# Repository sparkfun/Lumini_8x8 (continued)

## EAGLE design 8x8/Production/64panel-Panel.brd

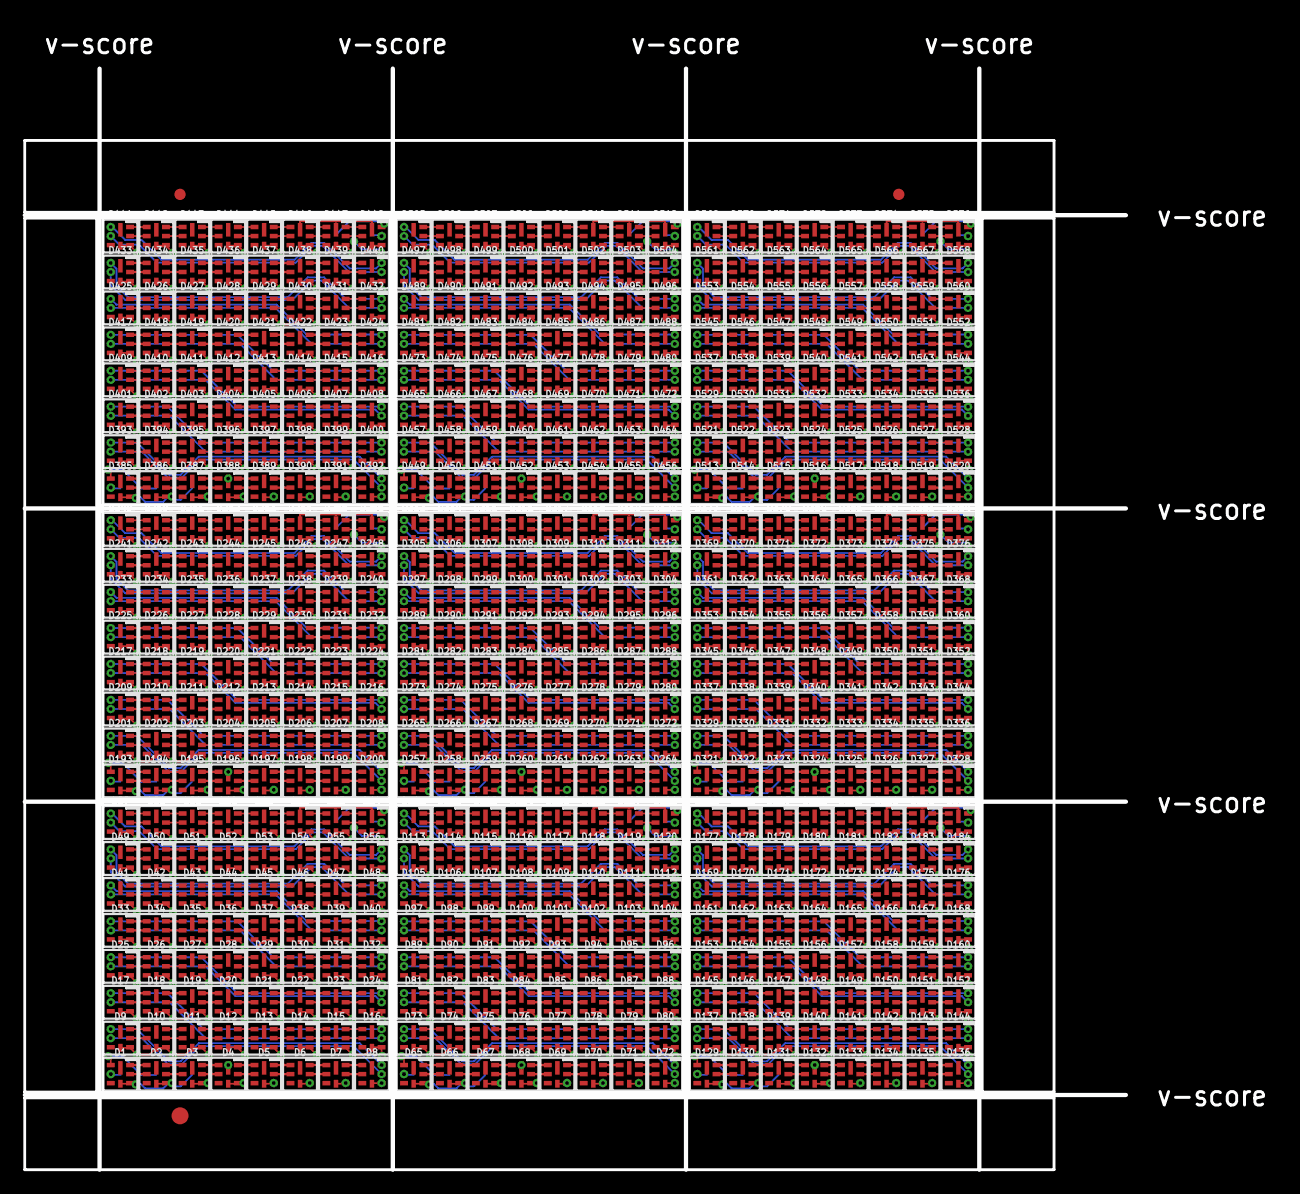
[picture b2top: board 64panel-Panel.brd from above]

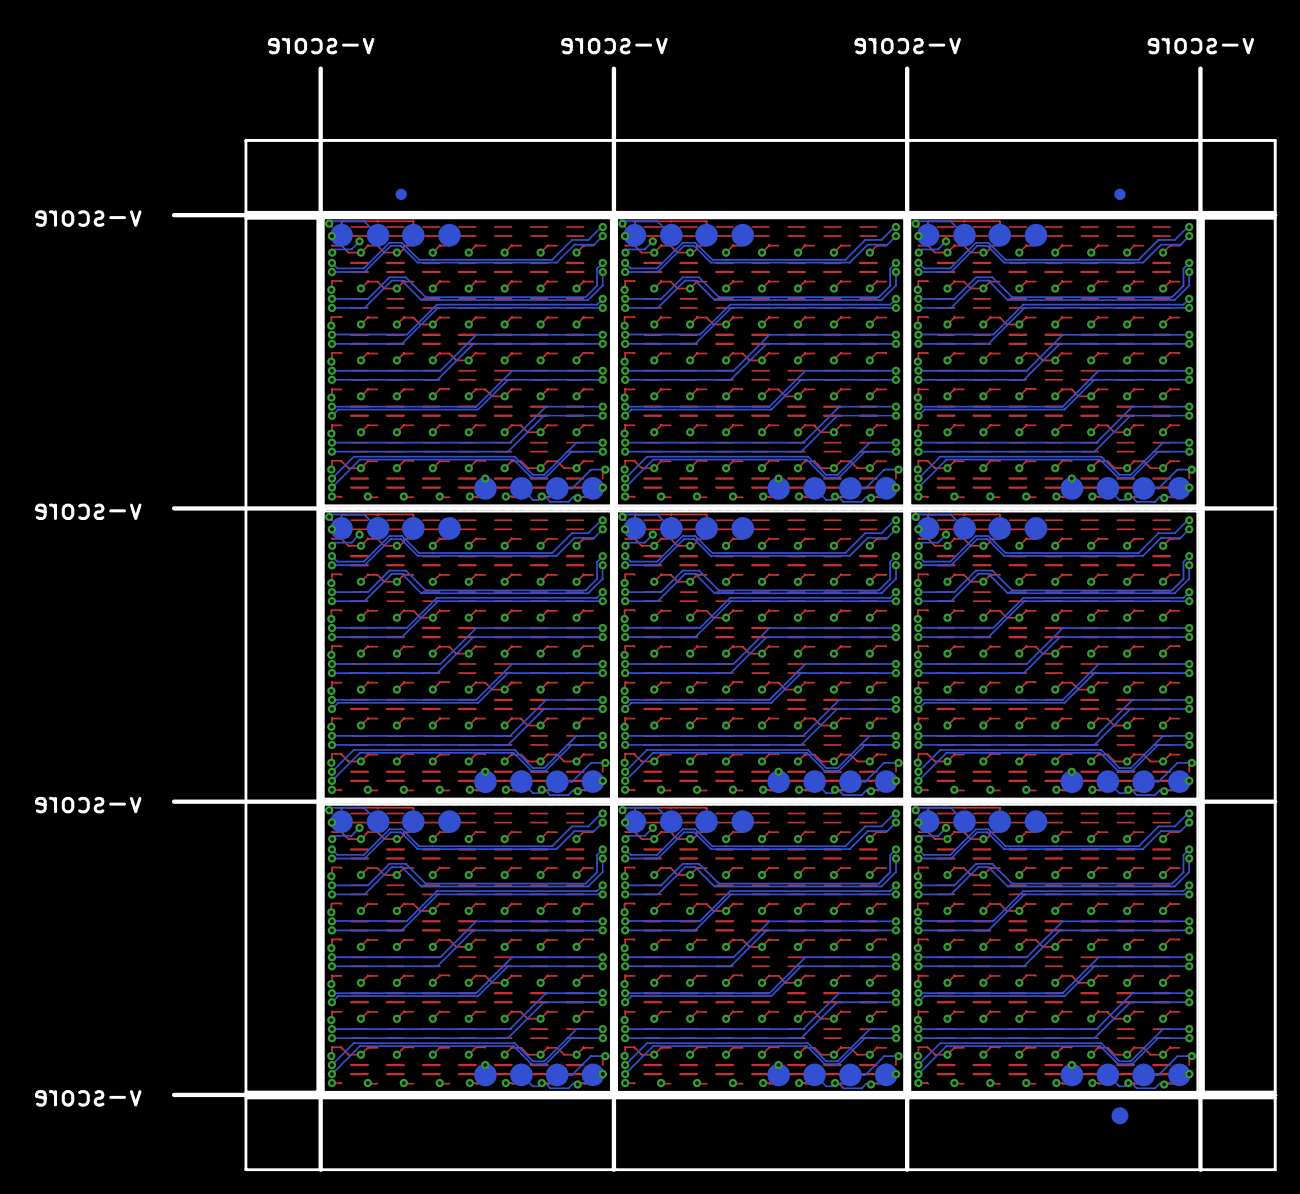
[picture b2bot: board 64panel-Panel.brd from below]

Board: 2 copper layers, 97.3 x 97.3 mm, 654 parts (75 on the bottom side), 1188 nets.

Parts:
D1, D2, D3, D4, D5, D6, D7, D8, D9, D10, D11, D12, D13, D14, D15, D16, D17, D18, D19, D20, D21, D22, D23, D24, D25, D26, D27, D28, D29, D30, D31, D32, D33, D34, D35, D36, D37, D38, D39, D40, D41, D42, D43, D44, D45, D46, D47, D48, D49, D50, D51, D52, D53, D54, D55, D56, D57, D58, D59, D60, D61, D62, D63, D64, D65, D66, D67, D68, D69, D70, D71, D72, D73, D74, D75, D76, D77, D78, D79, D80, D81, D82, D83, D84, D85, D86, D87, D88, D89, D90, D91, D92, D93, D94, D95, D96, D97, D98, D99, D100, D101, D102, D103, D104, D105, D106, D107, D108, D109, D110, D111, D112, D113, D114, D115, D116, D117, D118, D119, D120, D121, D122, D123, D124, D125, D126, D127, D128, D129, D130, D131, D132, D133, D134, D135, D136, D137, D138, D139, D140, D141, D142, D143, D144, D145, D146, D147, D148, D149, D150, D151, D152, D153, D154, D155, D156, D157, D158, D159, D160, D161, D162, D163, D164, D165, D166, D167, D168, D169, D170, D171, D172, D173, D174, D175, D176, D177, D178, D179, D180, D181, D182, D183, D184, D185, D186, D187, D188, D189, D190, D191, D192, D193, D194, D195, D196, D197, D198, D199, D200, D201, D202, D203, D204, D205, D206, D207, D208, D209, D210, D211, D212, D213, D214, D215, D216, D217, D218, D219, D220, D221, D222, D223, D224, D225, D226, D227, D228, D229, D230, D231, D232, D233, D234, D235, D236, D237, D238, D239, D240, D241, D242, D243, D244, D245, D246, D247, D248, D249, D250, D251, D252, D253, D254, D255, D256, D257, D258, D259, D260, D261, D262, D263, D264, D265, D266, D267, D268, D269, D270, D271, D272, D273, D274, D275, D276, D277, D278, D279, D280, D281, D282, D283, D284, D285, D286, D287, D288, D289, D290, D291, D292, D293, D294, D295, D296, D297, D298, D299, D300, D301, D302, D303, D304, D305, D306, D307, D308, D309, D310, D311, D312, D313, D314, D315, D316, D317, D318, D319, D320, D321, D322, D323, D324, D325, D326, D327, D328, D329, D330, D331, D332, D333, D334, D335, D336, D337, D338, D339, D340, D341, D342, D343, D344, D345, D346, D347, D348, D349, D350, D351, D352, D353, D354, D355, D356, D357, D358, D359, D360, D361, D362, D363, D364, D365, D366, D367, D368, D369, D370, D371, D372, D373, D374, D375, D376, D377, D378, D379, D380, D381, D382, D383, D384, D385, D386, D387, D388, D389, D390, D391, D392, D393, D394, D395, D396, D397, D398, D399, D400, D401, D402, D403, D404, D405, D406, D407, D408, D409, D410, D411, D412, D413, D414, D415, D416, D417, D418, D419, D420, D421, D422, D423, D424, D425, D426, D427, D428, D429, D430, D431, D432, D433, D434, D435, D436, D437, D438, D439, D440, D441, D442, D443, D444, D445, D446, D447, D448, D449, D450, D451, D452, D453, D454, D455, D456, D457, D458, D459, D460, D461, D462, D463, D464, D465, D466, D467, D468, D469, D470, D471, D472, D473, D474, D475, D476, D477, D478, D479, D480, D481, D482, D483, D484, D485, D486, D487, D488, D489, D490, D491, D492, D493, D494, D495, D496, D497, D498, D499, D500, D501, D502, D503, D504, D505, D506, D507, D508, D509, D510, D511, D512, D513, D514, D515, D516, D517, D518, D519, D520, D521, D522, D523, D524, D525, D526, D527, D528, D529, D530, D531, D532, D533, D534, D535, D536, D537, D538, D539, D540, D541, D542, D543, D544, D545, D546, D547, D548, D549, D550, D551, D552, D553, D554, D555, D556, D557, D558, D559, D560, D561, D562, D563, D564, D565, D566, D567, D568, D569, D570, D571, D572, D573, D574, D575, D576: APA1022020; APA102-2020
E$1, E$2, E$3, E$4: FIDUCIAL-1X2
E$5, E$6: FIDUCIAL-1.5X3
J1, J2, J3, J4, J5, J6, J7, J8, J9, J10, J11, J12, J13, J14, J15, J16, J17, J18, J19, J20, J21, J22, J23, J24, J25, J26, J27, J28, J29, J30, J31, J32, J33, J34, J35, J36, J37, J38, J39, J40, J41, J42, J43, J44, J45, J46, J47, J48, J49, J50, J51, J52, J53, J54, J55, J56, J57, J58, J59, J60, J61, J62, J63, J64, J65, J66, J67, J68, J69, J70, J71, J72: LED_PADCIRCULARPAD; CIRCULARPAD

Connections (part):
5V: D1.VDD, D1.VDDPAD, D2.VDD, D2.VDDPAD, D3.VDD, D3.VDDPAD, D4.VDD, D4.VDDPAD, D5.VDD, D5.VDDPAD, D6.VDD, D6.VDDPAD, D7.VDD, D7.VDDPAD, D8.VDD, D8.VDDPAD, D9.VDD, D9.VDDPAD, D10.VDD, D10.VDDPAD, D11.VDD, D11.VDDPAD, D12.VDD, D12.VDDPAD, D13.VDD, D13.VDDPAD, D14.VDD, D14.VDDPAD, D15.VDD, D15.VDDPAD, D16.VDD, D16.VDDPAD, D17.VDD, D17.VDDPAD, D18.VDD, D18.VDDPAD, D19.VDD, D19.VDDPAD, D20.VDD, D20.VDDPAD, D21.VDD, D21.VDDPAD, D22.VDD, D22.VDDPAD, D23.VDD, D23.VDDPAD, D24.VDD, D24.VDDPAD, D25.VDD, D25.VDDPAD, D26.VDD, D26.VDDPAD, D27.VDD, D27.VDDPAD, D28.VDD, D28.VDDPAD, D29.VDD, D29.VDDPAD, D30.VDD, D30.VDDPAD, D31.VDD, D31.VDDPAD, D32.VDD, D32.VDDPAD, D33.VDD, D33.VDDPAD, D34.VDD, D34.VDDPAD, D35.VDD, D35.VDDPAD, D36.VDD, D36.VDDPAD, D37.VDD, D37.VDDPAD, D38.VDD, D38.VDDPAD, D39.VDD, D39.VDDPAD, D40.VDD, D40.VDDPAD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
5V1: D65.VDD, D65.VDDPAD, D66.VDD, D66.VDDPAD, D67.VDD, D67.VDDPAD, D68.VDD, D68.VDDPAD, D69.VDD, D69.VDDPAD, D70.VDD, D70.VDDPAD, D71.VDD, D71.VDDPAD, D72.VDD, D72.VDDPAD, D73.VDD, D73.VDDPAD, D74.VDD, D74.VDDPAD, D75.VDD, D75.VDDPAD, D76.VDD, D76.VDDPAD, D77.VDD, D77.VDDPAD, D78.VDD, D78.VDDPAD, D79.VDD, D79.VDDPAD, D80.VDD, D80.VDDPAD, D81.VDD, D81.VDDPAD, D82.VDD, D82.VDDPAD, D83.VDD, D83.VDDPAD, D84.VDD, D84.VDDPAD, D85.VDD, D85.VDDPAD, D86.VDD, D86.VDDPAD, D87.VDD, D87.VDDPAD, D88.VDD, D88.VDDPAD, D89.VDD, D89.VDDPAD, D90.VDD, D90.VDDPAD, D91.VDD, D91.VDDPAD, D92.VDD, D92.VDDPAD, D93.VDD, D93.VDDPAD, D94.VDD, D94.VDDPAD, D95.VDD, D95.VDDPAD, D96.VDD, D96.VDDPAD, D97.VDD, D97.VDDPAD, D98.VDD, D98.VDDPAD, D99.VDD, D99.VDDPAD, D100.VDD, D100.VDDPAD, D101.VDD, D101.VDDPAD, D102.VDD, D102.VDDPAD, D103.VDD, D103.VDDPAD, D104.VDD, D104.VDDPAD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
5V2: D129.VDD, D129.VDDPAD, D130.VDD, D130.VDDPAD, D131.VDD, D131.VDDPAD, D132.VDD, D132.VDDPAD, D133.VDD, D133.VDDPAD, D134.VDD, D134.VDDPAD, D135.VDD, D135.VDDPAD, D136.VDD, D136.VDDPAD, D137.VDD, D137.VDDPAD, D138.VDD, D138.VDDPAD, D139.VDD, D139.VDDPAD, D140.VDD, D140.VDDPAD, D141.VDD, D141.VDDPAD, D142.VDD, D142.VDDPAD, D143.VDD, D143.VDDPAD, D144.VDD, D144.VDDPAD, D145.VDD, D145.VDDPAD, D146.VDD, D146.VDDPAD, D147.VDD, D147.VDDPAD, D148.VDD, D148.VDDPAD, D149.VDD, D149.VDDPAD, D150.VDD, D150.VDDPAD, D151.VDD, D151.VDDPAD, D152.VDD, D152.VDDPAD, D153.VDD, D153.VDDPAD, D154.VDD, D154.VDDPAD, D155.VDD, D155.VDDPAD, D156.VDD, D156.VDDPAD, D157.VDD, D157.VDDPAD, D158.VDD, D158.VDDPAD, D159.VDD, D159.VDDPAD, D160.VDD, D160.VDDPAD, D161.VDD, D161.VDDPAD, D162.VDD, D162.VDDPAD, D163.VDD, D163.VDDPAD, D164.VDD, D164.VDDPAD, D165.VDD, D165.VDDPAD, D166.VDD, D166.VDDPAD, D167.VDD, D167.VDDPAD, D168.VDD, D168.VDDPAD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
5V3: D193.VDD, D193.VDDPAD, D194.VDD, D194.VDDPAD, D195.VDD, D195.VDDPAD, D196.VDD, D196.VDDPAD, D197.VDD, D197.VDDPAD, D198.VDD, D198.VDDPAD, D199.VDD, D199.VDDPAD, D200.VDD, D200.VDDPAD, D201.VDD, D201.VDDPAD, D202.VDD, D202.VDDPAD, D203.VDD, D203.VDDPAD, D204.VDD, D204.VDDPAD, D205.VDD, D205.VDDPAD, D206.VDD, D206.VDDPAD, D207.VDD, D207.VDDPAD, D208.VDD, D208.VDDPAD, D209.VDD, D209.VDDPAD, D210.VDD, D210.VDDPAD, D211.VDD, D211.VDDPAD, D212.VDD, D212.VDDPAD, D213.VDD, D213.VDDPAD, D214.VDD, D214.VDDPAD, D215.VDD, D215.VDDPAD, D216.VDD, D216.VDDPAD, D217.VDD, D217.VDDPAD, D218.VDD, D218.VDDPAD, D219.VDD, D219.VDDPAD, D220.VDD, D220.VDDPAD, D221.VDD, D221.VDDPAD, D222.VDD, D222.VDDPAD, D223.VDD, D223.VDDPAD, D224.VDD, D224.VDDPAD, D225.VDD, D225.VDDPAD, D226.VDD, D226.VDDPAD, D227.VDD, D227.VDDPAD, D228.VDD, D228.VDDPAD, D229.VDD, D229.VDDPAD, D230.VDD, D230.VDDPAD, D231.VDD, D231.VDDPAD, D232.VDD, D232.VDDPAD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
5V4: D257.VDD, D257.VDDPAD, D258.VDD, D258.VDDPAD, D259.VDD, D259.VDDPAD, D260.VDD, D260.VDDPAD, D261.VDD, D261.VDDPAD, D262.VDD, D262.VDDPAD, D263.VDD, D263.VDDPAD, D264.VDD, D264.VDDPAD, D265.VDD, D265.VDDPAD, D266.VDD, D266.VDDPAD, D267.VDD, D267.VDDPAD, D268.VDD, D268.VDDPAD, D269.VDD, D269.VDDPAD, D270.VDD, D270.VDDPAD, D271.VDD, D271.VDDPAD, D272.VDD, D272.VDDPAD, D273.VDD, D273.VDDPAD, D274.VDD, D274.VDDPAD, D275.VDD, D275.VDDPAD, D276.VDD, D276.VDDPAD, D277.VDD, D277.VDDPAD, D278.VDD, D278.VDDPAD, D279.VDD, D279.VDDPAD, D280.VDD, D280.VDDPAD, D281.VDD, D281.VDDPAD, D282.VDD, D282.VDDPAD, D283.VDD, D283.VDDPAD, D284.VDD, D284.VDDPAD, D285.VDD, D285.VDDPAD, D286.VDD, D286.VDDPAD, D287.VDD, D287.VDDPAD, D288.VDD, D288.VDDPAD, D289.VDD, D289.VDDPAD, D290.VDD, D290.VDDPAD, D291.VDD, D291.VDDPAD, D292.VDD, D292.VDDPAD, D293.VDD, D293.VDDPAD, D294.VDD, D294.VDDPAD, D295.VDD, D295.VDDPAD, D296.VDD, D296.VDDPAD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
5V5: D321.VDD, D321.VDDPAD, D322.VDD, D322.VDDPAD, D323.VDD, D323.VDDPAD, D324.VDD, D324.VDDPAD, D325.VDD, D325.VDDPAD, D326.VDD, D326.VDDPAD, D327.VDD, D327.VDDPAD, D328.VDD, D328.VDDPAD, D329.VDD, D329.VDDPAD, D330.VDD, D330.VDDPAD, D331.VDD, D331.VDDPAD, D332.VDD, D332.VDDPAD, D333.VDD, D333.VDDPAD, D334.VDD, D334.VDDPAD, D335.VDD, D335.VDDPAD, D336.VDD, D336.VDDPAD, D337.VDD, D337.VDDPAD, D338.VDD, D338.VDDPAD, D339.VDD, D339.VDDPAD, D340.VDD, D340.VDDPAD, D341.VDD, D341.VDDPAD, D342.VDD, D342.VDDPAD, D343.VDD, D343.VDDPAD, D344.VDD, D344.VDDPAD, D345.VDD, D345.VDDPAD, D346.VDD, D346.VDDPAD, D347.VDD, D347.VDDPAD, D348.VDD, D348.VDDPAD, D349.VDD, D349.VDDPAD, D350.VDD, D350.VDDPAD, D351.VDD, D351.VDDPAD, D352.VDD, D352.VDDPAD, D353.VDD, D353.VDDPAD, D354.VDD, D354.VDDPAD, D355.VDD, D355.VDDPAD, D356.VDD, D356.VDDPAD, D357.VDD, D357.VDDPAD, D358.VDD, D358.VDDPAD, D359.VDD, D359.VDDPAD, D360.VDD, D360.VDDPAD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
5V6: D385.VDD, D385.VDDPAD, D386.VDD, D386.VDDPAD, D387.VDD, D387.VDDPAD, D388.VDD, D388.VDDPAD, D389.VDD, D389.VDDPAD, D390.VDD, D390.VDDPAD, D391.VDD, D391.VDDPAD, D392.VDD, D392.VDDPAD, D393.VDD, D393.VDDPAD, D394.VDD, D394.VDDPAD, D395.VDD, D395.VDDPAD, D396.VDD, D396.VDDPAD, D397.VDD, D397.VDDPAD, D398.VDD, D398.VDDPAD, D399.VDD, D399.VDDPAD, D400.VDD, D400.VDDPAD, D401.VDD, D401.VDDPAD, D402.VDD, D402.VDDPAD, D403.VDD, D403.VDDPAD, D404.VDD, D404.VDDPAD, D405.VDD, D405.VDDPAD, D406.VDD, D406.VDDPAD, D407.VDD, D407.VDDPAD, D408.VDD, D408.VDDPAD, D409.VDD, D409.VDDPAD, D410.VDD, D410.VDDPAD, D411.VDD, D411.VDDPAD, D412.VDD, D412.VDDPAD, D413.VDD, D413.VDDPAD, D414.VDD, D414.VDDPAD, D415.VDD, D415.VDDPAD, D416.VDD, D416.VDDPAD, D417.VDD, D417.VDDPAD, D418.VDD, D418.VDDPAD, D419.VDD, D419.VDDPAD, D420.VDD, D420.VDDPAD, D421.VDD, D421.VDDPAD, D422.VDD, D422.VDDPAD, D423.VDD, D423.VDDPAD, D424.VDD, D424.VDDPAD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
5V7: D449.VDD, D449.VDDPAD, D450.VDD, D450.VDDPAD, D451.VDD, D451.VDDPAD, D452.VDD, D452.VDDPAD, D453.VDD, D453.VDDPAD, D454.VDD, D454.VDDPAD, D455.VDD, D455.VDDPAD, D456.VDD, D456.VDDPAD, D457.VDD, D457.VDDPAD, D458.VDD, D458.VDDPAD, D459.VDD, D459.VDDPAD, D460.VDD, D460.VDDPAD, D461.VDD, D461.VDDPAD, D462.VDD, D462.VDDPAD, D463.VDD, D463.VDDPAD, D464.VDD, D464.VDDPAD, D465.VDD, D465.VDDPAD, D466.VDD, D466.VDDPAD, D467.VDD, D467.VDDPAD, D468.VDD, D468.VDDPAD, D469.VDD, D469.VDDPAD, D470.VDD, D470.VDDPAD, D471.VDD, D471.VDDPAD, D472.VDD, D472.VDDPAD, D473.VDD, D473.VDDPAD, D474.VDD, D474.VDDPAD, D475.VDD, D475.VDDPAD, D476.VDD, D476.VDDPAD, D477.VDD, D477.VDDPAD, D478.VDD, D478.VDDPAD, D479.VDD, D479.VDDPAD, D480.VDD, D480.VDDPAD, D481.VDD, D481.VDDPAD, D482.VDD, D482.VDDPAD, D483.VDD, D483.VDDPAD, D484.VDD, D484.VDDPAD, D485.VDD, D485.VDDPAD, D486.VDD, D486.VDDPAD, D487.VDD, D487.VDDPAD, D488.VDD, D488.VDDPAD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
5V8: D513.VDD, D513.VDDPAD, D514.VDD, D514.VDDPAD, D515.VDD, D515.VDDPAD, D516.VDD, D516.VDDPAD, D517.VDD, D517.VDDPAD, D518.VDD, D518.VDDPAD, D519.VDD, D519.VDDPAD, D520.VDD, D520.VDDPAD, D521.VDD, D521.VDDPAD, D522.VDD, D522.VDDPAD, D523.VDD, D523.VDDPAD, D524.VDD, D524.VDDPAD, D525.VDD, D525.VDDPAD, D526.VDD, D526.VDDPAD, D527.VDD, D527.VDDPAD, D528.VDD, D528.VDDPAD, D529.VDD, D529.VDDPAD, D530.VDD, D530.VDDPAD, D531.VDD, D531.VDDPAD, D532.VDD, D532.VDDPAD, D533.VDD, D533.VDDPAD, D534.VDD, D534.VDDPAD, D535.VDD, D535.VDDPAD, D536.VDD, D536.VDDPAD, D537.VDD, D537.VDDPAD, D538.VDD, D538.VDDPAD, D539.VDD, D539.VDDPAD, D540.VDD, D540.VDDPAD, D541.VDD, D541.VDDPAD, D542.VDD, D542.VDDPAD, D543.VDD, D543.VDDPAD, D544.VDD, D544.VDDPAD, D545.VDD, D545.VDDPAD, D546.VDD, D546.VDDPAD, D547.VDD, D547.VDDPAD, D548.VDD, D548.VDDPAD, D549.VDD, D549.VDDPAD, D550.VDD, D550.VDDPAD, D551.VDD, D551.VDDPAD, D552.VDD, D552.VDDPAD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
CI: D1.CKI, J4.P$1
CI1: D65.CKI, J12.P$1
CI2: D129.CKI, J20.P$1
CI3: D193.CKI, J28.P$1
CI4: D257.CKI, J36.P$1
CI5: D321.CKI, J44.P$1
CI6: D385.CKI, J52.P$1
CI7: D449.CKI, J60.P$1
CI8: D513.CKI, J68.P$1
CO: D64.CKO, J1.P$1
CO1: D128.CKO, J9.P$1
CO2: D192.CKO, J17.P$1
CO3: D256.CKO, J25.P$1
CO4: D320.CKO, J33.P$1
CO5: D384.CKO, J41.P$1
CO6: D448.CKO, J49.P$1
CO7: D512.CKO, J57.P$1
CO8: D576.CKO, J65.P$1
CT1: D9.CKO, D10.CKI
CT2: D18.CKO, D19.CKI
CT3: D27.CKO, D28.CKI
CT4: D36.CKO, D37.CKI
CT5: D45.CKO, D46.CKI
CT6: D54.CKO, D55.CKI
CT7: D63.CKO, D64.CKI
CT8: D127.CKO, D128.CKI
CT9: D73.CKO, D74.CKI
CT10: D82.CKO, D83.CKI
CT11: D91.CKO, D92.CKI
CT12: D100.CKO, D101.CKI
CT13: D109.CKO, D110.CKI
CT14: D118.CKO, D119.CKI
CT15: D191.CKO, D192.CKI
CT16: D137.CKO, D138.CKI
CT17: D146.CKO, D147.CKI
CT18: D155.CKO, D156.CKI
CT19: D164.CKO, D165.CKI
CT20: D173.CKO, D174.CKI
CT21: D182.CKO, D183.CKI
CT22: D255.CKO, D256.CKI
CT23: D201.CKO, D202.CKI
CT24: D210.CKO, D211.CKI
CT25: D219.CKO, D220.CKI
CT26: D228.CKO, D229.CKI
CT27: D237.CKO, D238.CKI
CT28: D246.CKO, D247.CKI
CT29: D319.CKO, D320.CKI
CT30: D265.CKO, D266.CKI
CT31: D274.CKO, D275.CKI
CT32: D283.CKO, D284.CKI
CT33: D292.CKO, D293.CKI
CT34: D301.CKO, D302.CKI
CT35: D310.CKO, D311.CKI
CT36: D383.CKO, D384.CKI
CT37: D329.CKO, D330.CKI
CT38: D338.CKO, D339.CKI
CT39: D347.CKO, D348.CKI
CT40: D356.CKO, D357.CKI
CT41: D365.CKO, D366.CKI
CT42: D374.CKO, D375.CKI
CT43: D447.CKO, D448.CKI
CT44: D393.CKO, D394.CKI
CT45: D402.CKO, D403.CKI
CT46: D411.CKO, D412.CKI
CT47: D420.CKO, D421.CKI
CT48: D429.CKO, D430.CKI
CT49: D438.CKO, D439.CKI
CT50: D511.CKO, D512.CKI
CT51: D457.CKO, D458.CKI
CT52: D466.CKO, D467.CKI
CT53: D475.CKO, D476.CKI
CT54: D484.CKO, D485.CKI
CT55: D493.CKO, D494.CKI
CT56: D502.CKO, D503.CKI
CT57: D575.CKO, D576.CKI
CT58: D521.CKO, D522.CKI
CT59: D530.CKO, D531.CKI
CT60: D539.CKO, D540.CKI
CT61: D548.CKO, D549.CKI
CT62: D557.CKO, D558.CKI
CT63: D566.CKO, D567.CKI
DI: D1.SDI, J3.P$1
DI1: D65.SDI, J11.P$1
DI2: D129.SDI, J19.P$1
DI3: D193.SDI, J27.P$1
DI4: D257.SDI, J35.P$1
DI5: D321.SDI, J43.P$1
DI6: D385.SDI, J51.P$1
DI7: D449.SDI, J59.P$1
DI8: D513.SDI, J67.P$1
DO: D64.SDO, J2.P$1
DO1: D128.SDO, J10.P$1
DO2: D192.SDO, J18.P$1
DO3: D256.SDO, J26.P$1
DO4: D320.SDO, J34.P$1
DO5: D384.SDO, J42.P$1
DO6: D448.SDO, J50.P$1
DO7: D512.SDO, J58.P$1
DO8: D576.SDO, J66.P$1
DT1: D9.SDO, D10.SDI
DT2: D18.SDO, D19.SDI
DT3: D27.SDO, D28.SDI
DT4: D36.SDO, D37.SDI
DT5: D45.SDO, D46.SDI
DT6: D54.SDO, D55.SDI
DT7: D63.SDO, D64.SDI
DT8: D127.SDO, D128.SDI
DT9: D73.SDO, D74.SDI
DT10: D82.SDO, D83.SDI
DT11: D91.SDO, D92.SDI
DT12: D100.SDO, D101.SDI
DT13: D109.SDO, D110.SDI
DT14: D118.SDO, D119.SDI
DT15: D191.SDO, D192.SDI
DT16: D137.SDO, D138.SDI
DT17: D146.SDO, D147.SDI
DT18: D155.SDO, D156.SDI
DT19: D164.SDO, D165.SDI
DT20: D173.SDO, D174.SDI
DT21: D182.SDO, D183.SDI
DT22: D255.SDO, D256.SDI
DT23: D201.SDO, D202.SDI
DT24: D210.SDO, D211.SDI
DT25: D219.SDO, D220.SDI
DT26: D228.SDO, D229.SDI
DT27: D237.SDO, D238.SDI
DT28: D246.SDO, D247.SDI
DT29: D319.SDO, D320.SDI
DT30: D265.SDO, D266.SDI
DT31: D274.SDO, D275.SDI
DT32: D283.SDO, D284.SDI
DT33: D292.SDO, D293.SDI
DT34: D301.SDO, D302.SDI
DT35: D310.SDO, D311.SDI
DT36: D383.SDO, D384.SDI
DT37: D329.SDO, D330.SDI
DT38: D338.SDO, D339.SDI
DT39: D347.SDO, D348.SDI
DT40: D356.SDO, D357.SDI
DT41: D365.SDO, D366.SDI
DT42: D374.SDO, D375.SDI
DT43: D447.SDO, D448.SDI
DT44: D393.SDO, D394.SDI
DT45: D402.SDO, D403.SDI
DT46: D411.SDO, D412.SDI
DT47: D420.SDO, D421.SDI
DT48: D429.SDO, D430.SDI
DT49: D438.SDO, D439.SDI
DT50: D511.SDO, D512.SDI
DT51: D457.SDO, D458.SDI
DT52: D466.SDO, D467.SDI
DT53: D475.SDO, D476.SDI
DT54: D484.SDO, D485.SDI
DT55: D493.SDO, D494.SDI
DT56: D502.SDO, D503.SDI
DT57: D575.SDO, D576.SDI
DT58: D521.SDO, D522.SDI
DT59: D530.SDO, D531.SDI
DT60: D539.SDO, D540.SDI
DT61: D548.SDO, D549.SDI
DT62: D557.SDO, D558.SDI
DT63: D566.SDO, D567.SDI
GND: D1.GND, D1.GNDPAD, D2.GND, D2.GNDPAD, D3.GND, D3.GNDPAD, D4.GND, D4.GNDPAD, D5.GND, D5.GNDPAD, D6.GND, D6.GNDPAD, D7.GND, D7.GNDPAD, D8.GND, D8.GNDPAD, D9.GND, D9.GNDPAD, D10.GND, D10.GNDPAD, D11.GND, D11.GNDPAD, D12.GND, D12.GNDPAD, D13.GND, D13.GNDPAD, D14.GND, D14.GNDPAD, D15.GND, D15.GNDPAD, D16.GND, D16.GNDPAD, D17.GND, D17.GNDPAD, D18.GND, D18.GNDPAD, D19.GND, D19.GNDPAD, D20.GND, D20.GNDPAD, D21.GND, D21.GNDPAD, D22.GND, D22.GNDPAD, D23.GND, D23.GNDPAD, D24.GND, D24.GNDPAD, D25.GND, D25.GNDPAD, D26.GND, D26.GNDPAD, D27.GND, D27.GNDPAD, D28.GND, D28.GNDPAD, D29.GND, D29.GNDPAD, D30.GND, D30.GNDPAD, D31.GND, D31.GNDPAD, D32.GND, D32.GNDPAD, D33.GND, D33.GNDPAD, D34.GND, D34.GNDPAD, D35.GND, D35.GNDPAD, D36.GND, D36.GNDPAD, D37.GND, D37.GNDPAD, D38.GND, D38.GNDPAD, D39.GND, D39.GNDPAD, D40.GND, D40.GNDPAD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
GND1: D65.GND, D65.GNDPAD, D66.GND, D66.GNDPAD, D67.GND, D67.GNDPAD, D68.GND, D68.GNDPAD, D69.GND, D69.GNDPAD, D70.GND, D70.GNDPAD, D71.GND, D71.GNDPAD, D72.GND, D72.GNDPAD, D73.GND, D73.GNDPAD, D74.GND, D74.GNDPAD, D75.GND, D75.GNDPAD, D76.GND, D76.GNDPAD, D77.GND, D77.GNDPAD, D78.GND, D78.GNDPAD, D79.GND, D79.GNDPAD, D80.GND, D80.GNDPAD, D81.GND, D81.GNDPAD, D82.GND, D82.GNDPAD, D83.GND, D83.GNDPAD, D84.GND, D84.GNDPAD, D85.GND, D85.GNDPAD, D86.GND, D86.GNDPAD, D87.GND, D87.GNDPAD, D88.GND, D88.GNDPAD, D89.GND, D89.GNDPAD, D90.GND, D90.GNDPAD, D91.GND, D91.GNDPAD, D92.GND, D92.GNDPAD, D93.GND, D93.GNDPAD, D94.GND, D94.GNDPAD, D95.GND, D95.GNDPAD, D96.GND, D96.GNDPAD, D97.GND, D97.GNDPAD, D98.GND, D98.GNDPAD, D99.GND, D99.GNDPAD, D100.GND, D100.GNDPAD, D101.GND, D101.GNDPAD, D102.GND, D102.GNDPAD, D103.GND, D103.GNDPAD, D104.GND, D104.GNDPAD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
GND2: D129.GND, D129.GNDPAD, D130.GND, D130.GNDPAD, D131.GND, D131.GNDPAD, D132.GND, D132.GNDPAD, D133.GND, D133.GNDPAD, D134.GND, D134.GNDPAD, D135.GND, D135.GNDPAD, D136.GND, D136.GNDPAD, D137.GND, D137.GNDPAD, D138.GND, D138.GNDPAD, D139.GND, D139.GNDPAD, D140.GND, D140.GNDPAD, D141.GND, D141.GNDPAD, D142.GND, D142.GNDPAD, D143.GND, D143.GNDPAD, D144.GND, D144.GNDPAD, D145.GND, D145.GNDPAD, D146.GND, D146.GNDPAD, D147.GND, D147.GNDPAD, D148.GND, D148.GNDPAD, D149.GND, D149.GNDPAD, D150.GND, D150.GNDPAD, D151.GND, D151.GNDPAD, D152.GND, D152.GNDPAD, D153.GND, D153.GNDPAD, D154.GND, D154.GNDPAD, D155.GND, D155.GNDPAD, D156.GND, D156.GNDPAD, D157.GND, D157.GNDPAD, D158.GND, D158.GNDPAD, D159.GND, D159.GNDPAD, D160.GND, D160.GNDPAD, D161.GND, D161.GNDPAD, D162.GND, D162.GNDPAD, D163.GND, D163.GNDPAD, D164.GND, D164.GNDPAD, D165.GND, D165.GNDPAD, D166.GND, D166.GNDPAD, D167.GND, D167.GNDPAD, D168.GND, D168.GNDPAD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
GND3: D193.GND, D193.GNDPAD, D194.GND, D194.GNDPAD, D195.GND, D195.GNDPAD, D196.GND, D196.GNDPAD, D197.GND, D197.GNDPAD, D198.GND, D198.GNDPAD, D199.GND, D199.GNDPAD, D200.GND, D200.GNDPAD, D201.GND, D201.GNDPAD, D202.GND, D202.GNDPAD, D203.GND, D203.GNDPAD, D204.GND, D204.GNDPAD, D205.GND, D205.GNDPAD, D206.GND, D206.GNDPAD, D207.GND, D207.GNDPAD, D208.GND, D208.GNDPAD, D209.GND, D209.GNDPAD, D210.GND, D210.GNDPAD, D211.GND, D211.GNDPAD, D212.GND, D212.GNDPAD, D213.GND, D213.GNDPAD, D214.GND, D214.GNDPAD, D215.GND, D215.GNDPAD, D216.GND, D216.GNDPAD, D217.GND, D217.GNDPAD, D218.GND, D218.GNDPAD, D219.GND, D219.GNDPAD, D220.GND, D220.GNDPAD, D221.GND, D221.GNDPAD, D222.GND, D222.GNDPAD, D223.GND, D223.GNDPAD, D224.GND, D224.GNDPAD, D225.GND, D225.GNDPAD, D226.GND, D226.GNDPAD, D227.GND, D227.GNDPAD, D228.GND, D228.GNDPAD, D229.GND, D229.GNDPAD, D230.GND, D230.GNDPAD, D231.GND, D231.GNDPAD, D232.GND, D232.GNDPAD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
GND4: D257.GND, D257.GNDPAD, D258.GND, D258.GNDPAD, D259.GND, D259.GNDPAD, D260.GND, D260.GNDPAD, D261.GND, D261.GNDPAD, D262.GND, D262.GNDPAD, D263.GND, D263.GNDPAD, D264.GND, D264.GNDPAD, D265.GND, D265.GNDPAD, D266.GND, D266.GNDPAD, D267.GND, D267.GNDPAD, D268.GND, D268.GNDPAD, D269.GND, D269.GNDPAD, D270.GND, D270.GNDPAD, D271.GND, D271.GNDPAD, D272.GND, D272.GNDPAD, D273.GND, D273.GNDPAD, D274.GND, D274.GNDPAD, D275.GND, D275.GNDPAD, D276.GND, D276.GNDPAD, D277.GND, D277.GNDPAD, D278.GND, D278.GNDPAD, D279.GND, D279.GNDPAD, D280.GND, D280.GNDPAD, D281.GND, D281.GNDPAD, D282.GND, D282.GNDPAD, D283.GND, D283.GNDPAD, D284.GND, D284.GNDPAD, D285.GND, D285.GNDPAD, D286.GND, D286.GNDPAD, D287.GND, D287.GNDPAD, D288.GND, D288.GNDPAD, D289.GND, D289.GNDPAD, D290.GND, D290.GNDPAD, D291.GND, D291.GNDPAD, D292.GND, D292.GNDPAD, D293.GND, D293.GNDPAD, D294.GND, D294.GNDPAD, D295.GND, D295.GNDPAD, D296.GND, D296.GNDPAD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
GND5: D321.GND, D321.GNDPAD, D322.GND, D322.GNDPAD, D323.GND, D323.GNDPAD, D324.GND, D324.GNDPAD, D325.GND, D325.GNDPAD, D326.GND, D326.GNDPAD, D327.GND, D327.GNDPAD, D328.GND, D328.GNDPAD, D329.GND, D329.GNDPAD, D330.GND, D330.GNDPAD, D331.GND, D331.GNDPAD, D332.GND, D332.GNDPAD, D333.GND, D333.GNDPAD, D334.GND, D334.GNDPAD, D335.GND, D335.GNDPAD, D336.GND, D336.GNDPAD, D337.GND, D337.GNDPAD, D338.GND, D338.GNDPAD, D339.GND, D339.GNDPAD, D340.GND, D340.GNDPAD, D341.GND, D341.GNDPAD, D342.GND, D342.GNDPAD, D343.GND, D343.GNDPAD, D344.GND, D344.GNDPAD, D345.GND, D345.GNDPAD, D346.GND, D346.GNDPAD, D347.GND, D347.GNDPAD, D348.GND, D348.GNDPAD, D349.GND, D349.GNDPAD, D350.GND, D350.GNDPAD, D351.GND, D351.GNDPAD, D352.GND, D352.GNDPAD, D353.GND, D353.GNDPAD, D354.GND, D354.GNDPAD, D355.GND, D355.GNDPAD, D356.GND, D356.GNDPAD, D357.GND, D357.GNDPAD, D358.GND, D358.GNDPAD, D359.GND, D359.GNDPAD, D360.GND, D360.GNDPAD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
GND6: D385.GND, D385.GNDPAD, D386.GND, D386.GNDPAD, D387.GND, D387.GNDPAD, D388.GND, D388.GNDPAD, D389.GND, D389.GNDPAD, D390.GND, D390.GNDPAD, D391.GND, D391.GNDPAD, D392.GND, D392.GNDPAD, D393.GND, D393.GNDPAD, D394.GND, D394.GNDPAD, D395.GND, D395.GNDPAD, D396.GND, D396.GNDPAD, D397.GND, D397.GNDPAD, D398.GND, D398.GNDPAD, D399.GND, D399.GNDPAD, D400.GND, D400.GNDPAD, D401.GND, D401.GNDPAD, D402.GND, D402.GNDPAD, D403.GND, D403.GNDPAD, D404.GND, D404.GNDPAD, D405.GND, D405.GNDPAD, D406.GND, D406.GNDPAD, D407.GND, D407.GNDPAD, D408.GND, D408.GNDPAD, D409.GND, D409.GNDPAD, D410.GND, D410.GNDPAD, D411.GND, D411.GNDPAD, D412.GND, D412.GNDPAD, D413.GND, D413.GNDPAD, D414.GND, D414.GNDPAD, D415.GND, D415.GNDPAD, D416.GND, D416.GNDPAD, D417.GND, D417.GNDPAD, D418.GND, D418.GNDPAD, D419.GND, D419.GNDPAD, D420.GND, D420.GNDPAD, D421.GND, D421.GNDPAD, D422.GND, D422.GNDPAD, D423.GND, D423.GNDPAD, D424.GND, D424.GNDPAD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
GND7: D449.GND, D449.GNDPAD, D450.GND, D450.GNDPAD, D451.GND, D451.GNDPAD, D452.GND, D452.GNDPAD, D453.GND, D453.GNDPAD, D454.GND, D454.GNDPAD, D455.GND, D455.GNDPAD, D456.GND, D456.GNDPAD, D457.GND, D457.GNDPAD, D458.GND, D458.GNDPAD, D459.GND, D459.GNDPAD, D460.GND, D460.GNDPAD, D461.GND, D461.GNDPAD, D462.GND, D462.GNDPAD, D463.GND, D463.GNDPAD, D464.GND, D464.GNDPAD, D465.GND, D465.GNDPAD, D466.GND, D466.GNDPAD, D467.GND, D467.GNDPAD, D468.GND, D468.GNDPAD, D469.GND, D469.GNDPAD, D470.GND, D470.GNDPAD, D471.GND, D471.GNDPAD, D472.GND, D472.GNDPAD, D473.GND, D473.GNDPAD, D474.GND, D474.GNDPAD, D475.GND, D475.GNDPAD, D476.GND, D476.GNDPAD, D477.GND, D477.GNDPAD, D478.GND, D478.GNDPAD, D479.GND, D479.GNDPAD, D480.GND, D480.GNDPAD, D481.GND, D481.GNDPAD, D482.GND, D482.GNDPAD, D483.GND, D483.GNDPAD, D484.GND, D484.GNDPAD, D485.GND, D485.GNDPAD, D486.GND, D486.GNDPAD, D487.GND, D487.GNDPAD, D488.GND, D488.GNDPAD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
GND8: D513.GND, D513.GNDPAD, D514.GND, D514.GNDPAD, D515.GND, D515.GNDPAD, D516.GND, D516.GNDPAD, D517.GND, D517.GNDPAD, D518.GND, D518.GNDPAD, D519.GND, D519.GNDPAD, D520.GND, D520.GNDPAD, D521.GND, D521.GNDPAD, D522.GND, D522.GNDPAD, D523.GND, D523.GNDPAD, D524.GND, D524.GNDPAD, D525.GND, D525.GNDPAD, D526.GND, D526.GNDPAD, D527.GND, D527.GNDPAD, D528.GND, D528.GNDPAD, D529.GND, D529.GNDPAD, D530.GND, D530.GNDPAD, D531.GND, D531.GNDPAD, D532.GND, D532.GNDPAD, D533.GND, D533.GNDPAD, D534.GND, D534.GNDPAD, D535.GND, D535.GNDPAD, D536.GND, D536.GNDPAD, D537.GND, D537.GNDPAD, D538.GND, D538.GNDPAD, D539.GND, D539.GNDPAD, D540.GND, D540.GNDPAD, D541.GND, D541.GNDPAD, D542.GND, D542.GNDPAD, D543.GND, D543.GNDPAD, D544.GND, D544.GNDPAD, D545.GND, D545.GNDPAD, D546.GND, D546.GNDPAD, D547.GND, D547.GNDPAD, D548.GND, D548.GNDPAD, D549.GND, D549.GNDPAD, D550.GND, D550.GNDPAD, D551.GND, D551.GNDPAD, D552.GND, D552.GNDPAD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
unnamed: D1.SDO, D2.SDI
unnamed: D1.CKO, D2.CKI
unnamed: D65.SDO, D66.SDI
unnamed: D65.CKO, D66.CKI
unnamed: D2.SDO, D3.SDI
unnamed: D2.CKO, D3.CKI
unnamed: D3.SDO, D4.SDI
unnamed: D3.CKO, D4.CKI
unnamed: D4.SDO, D5.SDI
unnamed: D4.CKO, D5.CKI
unnamed: D5.SDO, D6.SDI
unnamed: D5.CKO, D6.CKI
unnamed: D6.SDO, D7.SDI
unnamed: D6.CKO, D7.CKI
unnamed: D7.SDO, D8.SDI
unnamed: D7.CKO, D8.CKI
unnamed: D8.SDO, D9.SDI
unnamed: D8.CKO, D9.CKI
unnamed: D66.SDO, D67.SDI
unnamed: D66.CKO, D67.CKI
unnamed: D10.SDO, D11.SDI
unnamed: D10.CKO, D11.CKI
unnamed: D11.SDO, D12.SDI
unnamed: D11.CKO, D12.CKI
unnamed: D12.SDO, D13.SDI
unnamed: D12.CKO, D13.CKI
unnamed: D13.SDO, D14.SDI
unnamed: D13.CKO, D14.CKI
unnamed: D14.SDO, D15.SDI
unnamed: D14.CKO, D15.CKI
unnamed: D15.SDO, D16.SDI
unnamed: D15.CKO, D16.CKI
unnamed: D16.SDO, D17.SDI
unnamed: D16.CKO, D17.CKI
unnamed: D17.SDO, D18.SDI
unnamed: D17.CKO, D18.CKI
unnamed: D19.SDO, D20.SDI
unnamed: D19.CKO, D20.CKI
unnamed: D20.SDO, D21.SDI
unnamed: D20.CKO, D21.CKI
unnamed: D21.SDO, D22.SDI
unnamed: D21.CKO, D22.CKI
unnamed: D22.SDO, D23.SDI
unnamed: D22.CKO, D23.CKI
unnamed: D23.SDO, D24.SDI
unnamed: D23.CKO, D24.CKI
unnamed: D24.SDO, D25.SDI
unnamed: D24.CKO, D25.CKI
unnamed: D25.SDO, D26.SDI
unnamed: D25.CKO, D26.CKI
unnamed: D26.SDO, D27.SDI
unnamed: D26.CKO, D27.CKI
unnamed: D28.SDO, D29.SDI
unnamed: D28.CKO, D29.CKI
unnamed: D29.SDO, D30.SDI
unnamed: D29.CKO, D30.CKI
unnamed: D30.SDO, D31.SDI
unnamed: D30.CKO, D31.CKI
unnamed: D31.SDO, D32.SDI
unnamed: D31.CKO, D32.CKI
unnamed: D32.SDO, D33.SDI
unnamed: D32.CKO, D33.CKI
unnamed: D33.SDO, D34.SDI
unnamed: D33.CKO, D34.CKI
unnamed: D34.SDO, D35.SDI
unnamed: D34.CKO, D35.CKI
unnamed: D35.SDO, D36.SDI
unnamed: D35.CKO, D36.CKI
unnamed: D37.SDO, D38.SDI
unnamed: D37.CKO, D38.CKI
unnamed: D38.SDO, D39.SDI
unnamed: D38.CKO, D39.CKI
unnamed: D39.SDO, D40.SDI
unnamed: D39.CKO, D40.CKI
unnamed: D40.SDO, D41.SDI
unnamed: D40.CKO, D41.CKI
unnamed: D41.SDO, D42.SDI
unnamed: D41.CKO, D42.CKI
unnamed: D42.SDO, D43.SDI
unnamed: D42.CKO, D43.CKI
unnamed: D43.SDO, D44.SDI
unnamed: D43.CKO, D44.CKI
unnamed: D44.SDO, D45.SDI
unnamed: D44.CKO, D45.CKI
unnamed: D46.SDO, D47.SDI
unnamed: D46.CKO, D47.CKI
unnamed: D47.SDO, D48.SDI
unnamed: D47.CKO, D48.CKI
unnamed: D48.SDO, D49.SDI
unnamed: D48.CKO, D49.CKI
unnamed: D49.SDO, D50.SDI
unnamed: D49.CKO, D50.CKI
unnamed: D50.SDO, D51.SDI
unnamed: D50.CKO, D51.CKI
unnamed: D51.SDO, D52.SDI
unnamed: D51.CKO, D52.CKI
unnamed: D52.SDO, D53.SDI
unnamed: D52.CKO, D53.CKI
unnamed: D53.SDO, D54.SDI
unnamed: D53.CKO, D54.CKI
unnamed: D55.SDO, D56.SDI
unnamed: D55.CKO, D56.CKI
unnamed: D56.SDO, D57.SDI
unnamed: D56.CKO, D57.CKI
unnamed: D57.SDO, D58.SDI
unnamed: D57.CKO, D58.CKI
unnamed: D58.SDO, D59.SDI
unnamed: D58.CKO, D59.CKI
unnamed: D59.SDO, D60.SDI
unnamed: D59.CKO, D60.CKI
unnamed: D60.SDO, D61.SDI
unnamed: D60.CKO, D61.CKI
unnamed: D61.SDO, D62.SDI
unnamed: D61.CKO, D62.CKI
unnamed: D62.SDO, D63.SDI
unnamed: D62.CKO, D63.CKI
unnamed: D67.SDO, D68.SDI
unnamed: D67.CKO, D68.CKI
unnamed: D68.SDO, D69.SDI
unnamed: D68.CKO, D69.CKI
unnamed: D69.SDO, D70.SDI
unnamed: D69.CKO, D70.CKI
unnamed: D70.SDO, D71.SDI
unnamed: D70.CKO, D71.CKI
unnamed: D71.SDO, D72.SDI
unnamed: D71.CKO, D72.CKI
unnamed: D72.SDO, D73.SDI
unnamed: D72.CKO, D73.CKI
unnamed: D74.SDO, D75.SDI
unnamed: D74.CKO, D75.CKI
unnamed: D75.SDO, D76.SDI
unnamed: D75.CKO, D76.CKI
unnamed: D76.SDO, D77.SDI
unnamed: D76.CKO, D77.CKI
unnamed: D77.SDO, D78.SDI
unnamed: D77.CKO, D78.CKI
unnamed: D78.SDO, D79.SDI
unnamed: D78.CKO, D79.CKI
unnamed: D79.SDO, D80.SDI
unnamed: D79.CKO, D80.CKI
unnamed: D80.SDO, D81.SDI
unnamed: D80.CKO, D81.CKI
unnamed: D81.SDO, D82.SDI
unnamed: D81.CKO, D82.CKI
unnamed: D83.SDO, D84.SDI
unnamed: D83.CKO, D84.CKI
unnamed: D84.SDO, D85.SDI
unnamed: D84.CKO, D85.CKI
unnamed: D85.SDO, D86.SDI
unnamed: D85.CKO, D86.CKI
unnamed: D86.SDO, D87.SDI
unnamed: D86.CKO, D87.CKI
unnamed: D87.SDO, D88.SDI
unnamed: D87.CKO, D88.CKI
unnamed: D88.SDO, D89.SDI
unnamed: D88.CKO, D89.CKI
unnamed: D89.SDO, D90.SDI
unnamed: D89.CKO, D90.CKI
unnamed: D90.SDO, D91.SDI
unnamed: D90.CKO, D91.CKI
unnamed: D92.SDO, D93.SDI
unnamed: D92.CKO, D93.CKI
unnamed: D93.SDO, D94.SDI
unnamed: D93.CKO, D94.CKI
unnamed: D94.SDO, D95.SDI
unnamed: D94.CKO, D95.CKI
unnamed: D95.SDO, D96.SDI
unnamed: D95.CKO, D96.CKI
unnamed: D96.SDO, D97.SDI
unnamed: D96.CKO, D97.CKI
unnamed: D97.SDO, D98.SDI
unnamed: D97.CKO, D98.CKI
unnamed: D98.SDO, D99.SDI
unnamed: D98.CKO, D99.CKI
unnamed: D99.SDO, D100.SDI
unnamed: D99.CKO, D100.CKI
unnamed: D101.SDO, D102.SDI
unnamed: D101.CKO, D102.CKI
unnamed: D102.SDO, D103.SDI
unnamed: D102.CKO, D103.CKI
unnamed: D103.SDO, D104.SDI
unnamed: D103.CKO, D104.CKI
unnamed: D104.SDO, D105.SDI
unnamed: D104.CKO, D105.CKI
unnamed: D105.SDO, D106.SDI
unnamed: D105.CKO, D106.CKI
unnamed: D106.SDO, D107.SDI
unnamed: D106.CKO, D107.CKI
unnamed: D107.SDO, D108.SDI
unnamed: D107.CKO, D108.CKI
unnamed: D108.SDO, D109.SDI
unnamed: D108.CKO, D109.CKI
unnamed: D110.SDO, D111.SDI
unnamed: D110.CKO, D111.CKI
unnamed: D111.SDO, D112.SDI
unnamed: D111.CKO, D112.CKI
unnamed: D112.SDO, D113.SDI
unnamed: D112.CKO, D113.CKI
unnamed: D113.SDO, D114.SDI
unnamed: D113.CKO, D114.CKI
unnamed: D114.SDO, D115.SDI
unnamed: D114.CKO, D115.CKI
unnamed: D115.SDO, D116.SDI
unnamed: D115.CKO, D116.CKI
unnamed: D116.SDO, D117.SDI
unnamed: D116.CKO, D117.CKI
unnamed: D117.SDO, D118.SDI
unnamed: D117.CKO, D118.CKI
unnamed: D119.SDO, D120.SDI
unnamed: D119.CKO, D120.CKI
unnamed: D120.SDO, D121.SDI
unnamed: D120.CKO, D121.CKI
unnamed: D121.SDO, D122.SDI
unnamed: D121.CKO, D122.CKI
unnamed: D122.SDO, D123.SDI
unnamed: D122.CKO, D123.CKI
unnamed: D123.SDO, D124.SDI
unnamed: D123.CKO, D124.CKI
unnamed: D124.SDO, D125.SDI
unnamed: D124.CKO, D125.CKI
unnamed: D125.SDO, D126.SDI
unnamed: D125.CKO, D126.CKI
unnamed: D126.SDO, D127.SDI
unnamed: D126.CKO, D127.CKI
unnamed: D129.SDO, D130.SDI
unnamed: D129.CKO, D130.CKI
unnamed: D130.SDO, D131.SDI
unnamed: D130.CKO, D131.CKI
unnamed: D131.SDO, D132.SDI
unnamed: D131.CKO, D132.CKI
unnamed: D132.SDO, D133.SDI
unnamed: D132.CKO, D133.CKI
unnamed: D133.SDO, D134.SDI
unnamed: D133.CKO, D134.CKI
unnamed: D134.SDO, D135.SDI
unnamed: D134.CKO, D135.CKI
unnamed: D135.SDO, D136.SDI
unnamed: D135.CKO, D136.CKI
unnamed: D136.SDO, D137.SDI
unnamed: D136.CKO, D137.CKI
unnamed: D138.SDO, D139.SDI
unnamed: D138.CKO, D139.CKI
unnamed: D139.SDO, D140.SDI
unnamed: D139.CKO, D140.CKI
unnamed: D140.SDO, D141.SDI
unnamed: D140.CKO, D141.CKI
unnamed: D141.SDO, D142.SDI
unnamed: D141.CKO, D142.CKI
unnamed: D142.SDO, D143.SDI
unnamed: D142.CKO, D143.CKI
unnamed: D143.SDO, D144.SDI
unnamed: D143.CKO, D144.CKI
unnamed: D144.SDO, D145.SDI
unnamed: D144.CKO, D145.CKI
unnamed: D145.SDO, D146.SDI
unnamed: D145.CKO, D146.CKI
unnamed: D147.SDO, D148.SDI
unnamed: D147.CKO, D148.CKI
unnamed: D148.SDO, D149.SDI
unnamed: D148.CKO, D149.CKI
unnamed: D149.SDO, D150.SDI
unnamed: D149.CKO, D150.CKI
unnamed: D150.SDO, D151.SDI
unnamed: D150.CKO, D151.CKI
unnamed: D151.SDO, D152.SDI
unnamed: D151.CKO, D152.CKI
unnamed: D152.SDO, D153.SDI
unnamed: D152.CKO, D153.CKI
unnamed: D153.SDO, D154.SDI
unnamed: D153.CKO, D154.CKI
unnamed: D154.SDO, D155.SDI
unnamed: D154.CKO, D155.CKI
unnamed: D156.SDO, D157.SDI
unnamed: D156.CKO, D157.CKI
unnamed: D157.SDO, D158.SDI
unnamed: D157.CKO, D158.CKI
unnamed: D158.SDO, D159.SDI
unnamed: D158.CKO, D159.CKI
unnamed: D159.SDO, D160.SDI
unnamed: D159.CKO, D160.CKI
unnamed: D160.SDO, D161.SDI
unnamed: D160.CKO, D161.CKI
unnamed: D161.SDO, D162.SDI
unnamed: D161.CKO, D162.CKI
unnamed: D162.SDO, D163.SDI
unnamed: D162.CKO, D163.CKI
unnamed: D163.SDO, D164.SDI
unnamed: D163.CKO, D164.CKI
unnamed: D165.SDO, D166.SDI
unnamed: D165.CKO, D166.CKI
unnamed: D166.SDO, D167.SDI
unnamed: D166.CKO, D167.CKI
unnamed: D167.SDO, D168.SDI
unnamed: D167.CKO, D168.CKI
unnamed: D168.SDO, D169.SDI
unnamed: D168.CKO, D169.CKI
unnamed: D169.SDO, D170.SDI
unnamed: D169.CKO, D170.CKI
unnamed: D170.SDO, D171.SDI
unnamed: D170.CKO, D171.CKI
unnamed: D171.SDO, D172.SDI
unnamed: D171.CKO, D172.CKI
unnamed: D172.SDO, D173.SDI
unnamed: D172.CKO, D173.CKI
unnamed: D174.SDO, D175.SDI
unnamed: D174.CKO, D175.CKI
unnamed: D175.SDO, D176.SDI
unnamed: D175.CKO, D176.CKI
unnamed: D176.SDO, D177.SDI
unnamed: D176.CKO, D177.CKI
unnamed: D177.SDO, D178.SDI
unnamed: D177.CKO, D178.CKI
unnamed: D178.SDO, D179.SDI
unnamed: D178.CKO, D179.CKI
unnamed: D179.SDO, D180.SDI
unnamed: D179.CKO, D180.CKI
unnamed: D180.SDO, D181.SDI
unnamed: D180.CKO, D181.CKI
unnamed: D181.SDO, D182.SDI
unnamed: D181.CKO, D182.CKI
unnamed: D183.SDO, D184.SDI
unnamed: D183.CKO, D184.CKI
unnamed: D184.SDO, D185.SDI
unnamed: D184.CKO, D185.CKI
unnamed: D185.SDO, D186.SDI
unnamed: D185.CKO, D186.CKI
unnamed: D186.SDO, D187.SDI
unnamed: D186.CKO, D187.CKI
unnamed: D187.SDO, D188.SDI
unnamed: D187.CKO, D188.CKI
unnamed: D188.SDO, D189.SDI
unnamed: D188.CKO, D189.CKI
unnamed: D189.SDO, D190.SDI
unnamed: D189.CKO, D190.CKI
unnamed: D190.SDO, D191.SDI
unnamed: D190.CKO, D191.CKI
unnamed: D193.SDO, D194.SDI
unnamed: D193.CKO, D194.CKI
unnamed: D194.SDO, D195.SDI
unnamed: D194.CKO, D195.CKI
unnamed: D195.SDO, D196.SDI
unnamed: D195.CKO, D196.CKI
unnamed: D196.SDO, D197.SDI
unnamed: D196.CKO, D197.CKI
unnamed: D197.SDO, D198.SDI
unnamed: D197.CKO, D198.CKI
unnamed: D198.SDO, D199.SDI
unnamed: D198.CKO, D199.CKI
unnamed: D199.SDO, D200.SDI
unnamed: D199.CKO, D200.CKI
unnamed: D200.SDO, D201.SDI
unnamed: D200.CKO, D201.CKI
unnamed: D202.SDO, D203.SDI
unnamed: D202.CKO, D203.CKI
unnamed: D203.SDO, D204.SDI
unnamed: D203.CKO, D204.CKI
unnamed: D204.SDO, D205.SDI
unnamed: D204.CKO, D205.CKI
unnamed: D205.SDO, D206.SDI
unnamed: D205.CKO, D206.CKI
unnamed: D206.SDO, D207.SDI
unnamed: D206.CKO, D207.CKI
unnamed: D207.SDO, D208.SDI
unnamed: D207.CKO, D208.CKI
unnamed: D208.SDO, D209.SDI
unnamed: D208.CKO, D209.CKI
unnamed: D209.SDO, D210.SDI
unnamed: D209.CKO, D210.CKI
unnamed: D211.SDO, D212.SDI
unnamed: D211.CKO, D212.CKI
unnamed: D212.SDO, D213.SDI
unnamed: D212.CKO, D213.CKI
unnamed: D213.SDO, D214.SDI
unnamed: D213.CKO, D214.CKI
unnamed: D214.SDO, D215.SDI
unnamed: D214.CKO, D215.CKI
unnamed: D215.SDO, D216.SDI
unnamed: D215.CKO, D216.CKI
unnamed: D216.SDO, D217.SDI
unnamed: D216.CKO, D217.CKI
unnamed: D217.SDO, D218.SDI
unnamed: D217.CKO, D218.CKI
unnamed: D218.SDO, D219.SDI
unnamed: D218.CKO, D219.CKI
unnamed: D220.SDO, D221.SDI
unnamed: D220.CKO, D221.CKI
unnamed: D221.SDO, D222.SDI
unnamed: D221.CKO, D222.CKI
unnamed: D222.SDO, D223.SDI
unnamed: D222.CKO, D223.CKI
unnamed: D223.SDO, D224.SDI
unnamed: D223.CKO, D224.CKI
unnamed: D224.SDO, D225.SDI
unnamed: D224.CKO, D225.CKI
unnamed: D225.SDO, D226.SDI
unnamed: D225.CKO, D226.CKI
unnamed: D226.SDO, D227.SDI
unnamed: D226.CKO, D227.CKI
unnamed: D227.SDO, D228.SDI
unnamed: D227.CKO, D228.CKI
unnamed: D229.SDO, D230.SDI
unnamed: D229.CKO, D230.CKI
unnamed: D230.SDO, D231.SDI
unnamed: D230.CKO, D231.CKI
unnamed: D231.SDO, D232.SDI
unnamed: D231.CKO, D232.CKI
unnamed: D232.SDO, D233.SDI
unnamed: D232.CKO, D233.CKI
unnamed: D233.SDO, D234.SDI
unnamed: D233.CKO, D234.CKI
unnamed: D234.SDO, D235.SDI
unnamed: D234.CKO, D235.CKI
unnamed: D235.SDO, D236.SDI
unnamed: D235.CKO, D236.CKI
unnamed: D236.SDO, D237.SDI
unnamed: D236.CKO, D237.CKI
unnamed: D238.SDO, D239.SDI
unnamed: D238.CKO, D239.CKI
unnamed: D239.SDO, D240.SDI
unnamed: D239.CKO, D240.CKI
unnamed: D240.SDO, D241.SDI
unnamed: D240.CKO, D241.CKI
unnamed: D241.SDO, D242.SDI
unnamed: D241.CKO, D242.CKI
unnamed: D242.SDO, D243.SDI
unnamed: D242.CKO, D243.CKI
unnamed: D243.SDO, D244.SDI
unnamed: D243.CKO, D244.CKI
unnamed: D244.SDO, D245.SDI
unnamed: D244.CKO, D245.CKI
unnamed: D245.SDO, D246.SDI
unnamed: D245.CKO, D246.CKI
unnamed: D247.SDO, D248.SDI
unnamed: D247.CKO, D248.CKI
unnamed: D248.SDO, D249.SDI
unnamed: D248.CKO, D249.CKI
unnamed: D249.SDO, D250.SDI
unnamed: D249.CKO, D250.CKI
unnamed: D250.SDO, D251.SDI
unnamed: D250.CKO, D251.CKI
unnamed: D251.SDO, D252.SDI
unnamed: D251.CKO, D252.CKI
unnamed: D252.SDO, D253.SDI
unnamed: D252.CKO, D253.CKI
unnamed: D253.SDO, D254.SDI
unnamed: D253.CKO, D254.CKI
unnamed: D254.SDO, D255.SDI
unnamed: D254.CKO, D255.CKI
unnamed: D257.SDO, D258.SDI
unnamed: D257.CKO, D258.CKI
unnamed: D258.SDO, D259.SDI
unnamed: D258.CKO, D259.CKI
unnamed: D259.SDO, D260.SDI
unnamed: D259.CKO, D260.CKI
unnamed: D260.SDO, D261.SDI
unnamed: D260.CKO, D261.CKI
unnamed: D261.SDO, D262.SDI
unnamed: D261.CKO, D262.CKI
unnamed: D262.SDO, D263.SDI
unnamed: D262.CKO, D263.CKI
unnamed: D263.SDO, D264.SDI
unnamed: D263.CKO, D264.CKI
unnamed: D264.SDO, D265.SDI
unnamed: D264.CKO, D265.CKI
unnamed: D266.SDO, D267.SDI
unnamed: D266.CKO, D267.CKI
unnamed: D267.SDO, D268.SDI
unnamed: D267.CKO, D268.CKI
unnamed: D268.SDO, D269.SDI
unnamed: D268.CKO, D269.CKI
unnamed: D269.SDO, D270.SDI
unnamed: D269.CKO, D270.CKI
unnamed: D270.SDO, D271.SDI
unnamed: D270.CKO, D271.CKI
unnamed: D271.SDO, D272.SDI
unnamed: D271.CKO, D272.CKI
unnamed: D272.SDO, D273.SDI
unnamed: D272.CKO, D273.CKI
unnamed: D273.SDO, D274.SDI
unnamed: D273.CKO, D274.CKI
unnamed: D275.SDO, D276.SDI
unnamed: D275.CKO, D276.CKI
unnamed: D276.SDO, D277.SDI
unnamed: D276.CKO, D277.CKI
unnamed: D277.SDO, D278.SDI
unnamed: D277.CKO, D278.CKI
unnamed: D278.SDO, D279.SDI
unnamed: D278.CKO, D279.CKI
unnamed: D279.SDO, D280.SDI
unnamed: D279.CKO, D280.CKI
unnamed: D280.SDO, D281.SDI
unnamed: D280.CKO, D281.CKI
unnamed: D281.SDO, D282.SDI
unnamed: D281.CKO, D282.CKI
unnamed: D282.SDO, D283.SDI
unnamed: D282.CKO, D283.CKI
unnamed: D284.SDO, D285.SDI
unnamed: D284.CKO, D285.CKI
unnamed: D285.SDO, D286.SDI
unnamed: D285.CKO, D286.CKI
unnamed: D286.SDO, D287.SDI
unnamed: D286.CKO, D287.CKI
unnamed: D287.SDO, D288.SDI
unnamed: D287.CKO, D288.CKI
unnamed: D288.SDO, D289.SDI
unnamed: D288.CKO, D289.CKI
unnamed: D289.SDO, D290.SDI
unnamed: D289.CKO, D290.CKI
unnamed: D290.SDO, D291.SDI
unnamed: D290.CKO, D291.CKI
unnamed: D291.SDO, D292.SDI
unnamed: D291.CKO, D292.CKI
unnamed: D293.SDO, D294.SDI
unnamed: D293.CKO, D294.CKI
unnamed: D294.SDO, D295.SDI
unnamed: D294.CKO, D295.CKI
unnamed: D295.SDO, D296.SDI
unnamed: D295.CKO, D296.CKI
unnamed: D296.SDO, D297.SDI
unnamed: D296.CKO, D297.CKI
unnamed: D297.SDO, D298.SDI
unnamed: D297.CKO, D298.CKI
unnamed: D298.SDO, D299.SDI
unnamed: D298.CKO, D299.CKI
unnamed: D299.SDO, D300.SDI
unnamed: D299.CKO, D300.CKI
unnamed: D300.SDO, D301.SDI
unnamed: D300.CKO, D301.CKI
unnamed: D302.SDO, D303.SDI
unnamed: D302.CKO, D303.CKI
unnamed: D303.SDO, D304.SDI
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
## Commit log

2018-09-14 routing 8x8
2018-09-19 finished laying out board, ordered panels
2018-10-15 changing to 6-pin
2018-10-15 updating repo structure
2018-10-17 pre design review
2018-10-23 updating to 4 layer
2018-10-24 changing heatsinks back to ground
2018-10-24 4 layer PCB note
2018-12-04 updating to proper footprint
2018-12-12 updating to new silk footprint for additional clarity
2018-12-13 removing problem vias
2018-12-20 updating copper to v10
2019-01-16 adding example code
2019-01-17 adding xy assignment example
2019-01-21 updating LuMini examples
2019-01-21 Updating 4th example to change width and height
2019-01-23 updating readme
